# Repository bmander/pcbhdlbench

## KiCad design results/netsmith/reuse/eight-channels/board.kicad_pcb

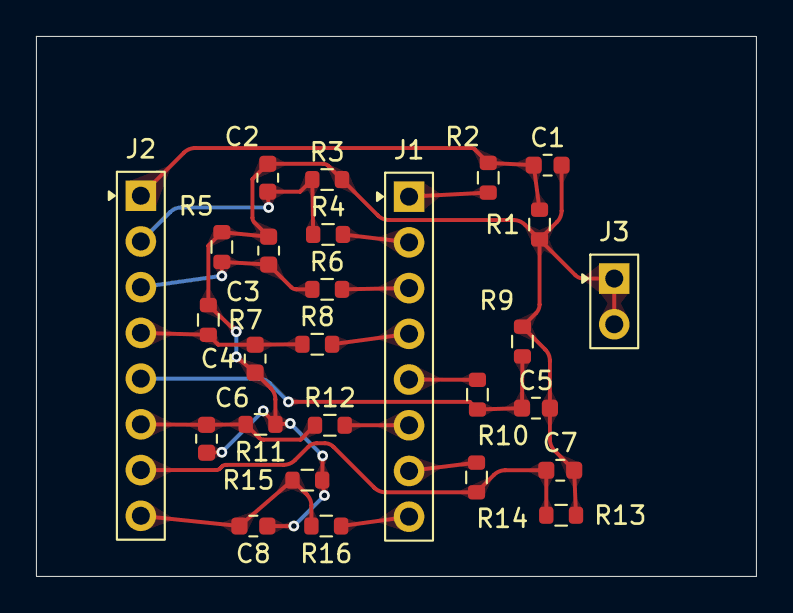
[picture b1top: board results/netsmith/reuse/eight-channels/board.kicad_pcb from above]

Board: 2 copper layers, 40.0 x 30.0 mm, 27 parts (0 on the bottom side), 17 nets.

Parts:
C1, C2, C3, C4, C5, C6, C7, C8: 100n; C_0603_1608Metric
J1, J2: Conn_01x08; PinHeader_1x08_P2.54mm_Vertical
J3: Conn_01x02; PinHeader_1x02_P2.54mm_Vertical
R1, R3, R5, R7, R9, R11, R13, R15: 100k; R_0603_1608Metric
R2, R4, R6, R8, R10, R12, R14, R16: 1k; R_0603_1608Metric

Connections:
net-ch1.c.a: C1.1, J2.1, R1.1, R2.2
net-ch1.c.b: C1.2, C2.2, C3.2, C4.2, C5.2, C6.2, C7.2, C8.2, J3.1, J3.2, R1.2, R3.2, R5.2, R7.2, R9.2, R11.2, R13.2, R15.2
net-ch1.rs.a: J1.1, R2.1
net-ch2.c.a: C2.1, J2.2, R3.1, R4.2
net-ch2.rs.a: J1.2, R4.1
net-ch3.c.a: C3.1, J2.3, R5.1, R6.2
net-ch3.rs.a: J1.3, R6.1
net-ch4.c.a: C4.1, J2.4, R7.1, R8.2
net-ch4.rs.a: J1.4, R8.1
net-ch5.c.a: C5.1, J2.5, R9.1, R10.2
net-ch5.rs.a: J1.5, R10.1
net-ch6.c.a: C6.1, J2.6, R11.1, R12.2
net-ch6.rs.a: J1.6, R12.1
net-ch7.c.a: C7.1, J2.7, R13.1, R14.2
net-ch7.rs.a: J1.7, R14.1
net-ch8.c.a: C8.1, J2.8, R15.1, R16.2
net-ch8.rs.a: J1.8, R16.1

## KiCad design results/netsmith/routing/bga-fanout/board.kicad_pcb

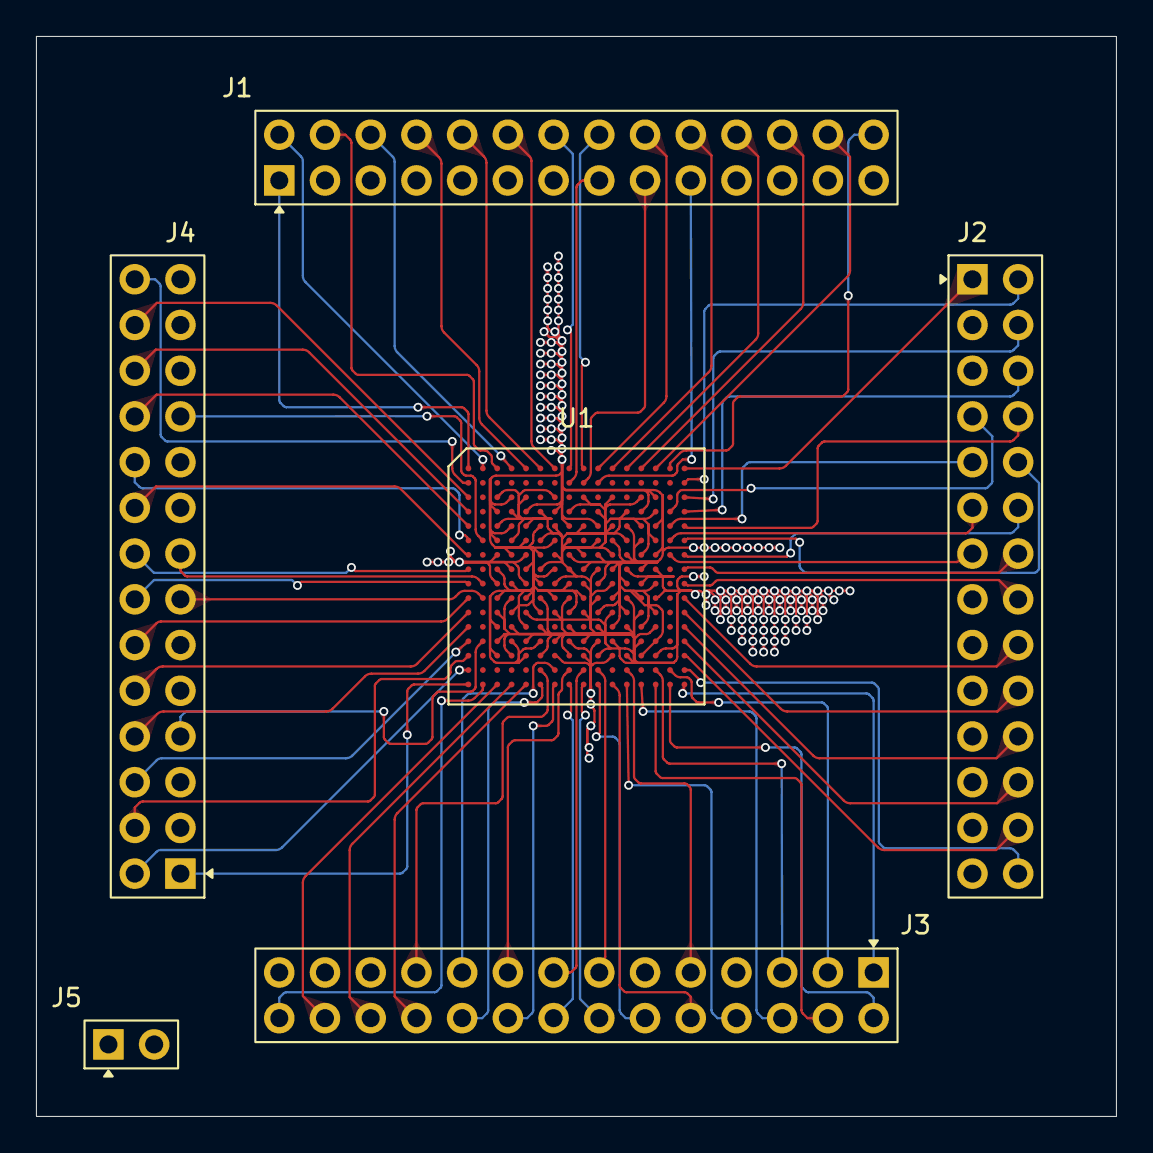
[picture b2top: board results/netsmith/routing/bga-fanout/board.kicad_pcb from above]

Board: 4 copper layers, 60.0 x 60.0 mm, 6 parts (0 on the bottom side), 114 nets.

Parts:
J1, J2, J3, J4: Header2x14; PinHeader_pins14_pitch2.54mm_rows2
J5: Conn_01x02; PinHeader_1x02_P2.54mm_Vertical
U1: Bga256; BGA-256_14.0x14.0mm_Layout16x16_P0.8mm_Ball0.45mm_Pad0.32mm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

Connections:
GND: J5.2, U1.C3, U1.C5, U1.C7, U1.C9, U1.C11, U1.C13, U1.D4, U1.D6, U1.D8, U1.D10, U1.D12, U1.D14, U1.E3, U1.E5, U1.E7, U1.E9, U1.E11, U1.E13, U1.F4, U1.F6, U1.F8, U1.F10, U1.F12, U1.F14, U1.G3, U1.G5, U1.G7, U1.G9, U1.G11, U1.G13, U1.H4, U1.H6, U1.H8, U1.H10, U1.H12, U1.H14, U1.J3, U1.J5, U1.J7, U1.J9, U1.J11, U1.J13, U1.K4, U1.K6, U1.K8, U1.K10, U1.K12, U1.K14, U1.L3, U1.L5, U1.L7, U1.L9, U1.L11, U1.L13, U1.M4, U1.M6, U1.M8, U1.M10, U1.M12, U1.M14, U1.N3, U1.N5, U1.N7, U1.N9, U1.N11, U1.N13, U1.P4, U1.P6, U1.P8, U1.P10, U1.P12, U1.P14
VCC: J5.1, U1.C4, U1.C6, U1.C8, U1.C10, U1.C12, U1.C14, U1.D3, U1.D5, U1.D7, U1.D9, U1.D11, U1.D13, U1.E4, U1.E6, U1.E8, U1.E10, U1.E12, U1.E14, U1.F3, U1.F5, U1.F7, U1.F9, U1.F11, U1.F13, U1.G4, U1.G6, U1.G8, U1.G10, U1.G12, U1.G14, U1.H3, U1.H5, U1.H7, U1.H9, U1.H11, U1.H13, U1.J4, U1.J6, U1.J8, U1.J10, U1.J12, U1.J14, U1.K3, U1.K5, U1.K7, U1.K9, U1.K11, U1.K13, U1.L4, U1.L6, U1.L8, U1.L10, U1.L12, U1.L14, U1.M3, U1.M5, U1.M7, U1.M9, U1.M11, U1.M13, U1.N4, U1.N6, U1.N8, U1.N10, U1.N12, U1.N14, U1.P3, U1.P5, U1.P7, U1.P9, U1.P11, U1.P13
net-j1.p1: J1.1, U1.A1
net-j1.p2: J1.2, U1.A2
net-j1.p3: J1.3, U1.B2
net-j1.p4: J1.4, U1.A3
net-j1.p5: J1.5, U1.B3
net-j1.p6: J1.6, U1.A4
net-j1.p7: J1.7, U1.B4
net-j1.p8: J1.8, U1.A5
net-j1.p9: J1.9, U1.B5
net-j1.p10: J1.10, U1.A6
net-j1.p11: J1.11, U1.B6
net-j1.p12: J1.12, U1.A7
net-j1.p13: J1.13, U1.B7
net-j1.p14: J1.14, U1.A8
net-j1.p15: J1.15, U1.B8
net-j1.p16: J1.16, U1.A9
net-j1.p17: J1.17, U1.B9
net-j1.p18: J1.18, U1.A10
net-j1.p19: J1.19, U1.B10
net-j1.p20: J1.20, U1.A11
net-j1.p21: J1.21, U1.B11
net-j1.p22: J1.22, U1.A12
net-j1.p23: J1.23, U1.B12
net-j1.p24: J1.24, U1.A13
net-j1.p25: J1.25, U1.B13
net-j1.p26: J1.26, U1.A14
net-j1.p27: J1.27, U1.B14
net-j1.p28: J1.28, U1.A15
net-j2.p1: J2.1, U1.A16
net-j2.p2: J2.2, U1.B16
net-j2.p3: J2.3, U1.B15
net-j2.p4: J2.4, U1.C16
net-j2.p5: J2.5, U1.C15
net-j2.p6: J2.6, U1.D16
net-j2.p7: J2.7, U1.D15
net-j2.p8: J2.8, U1.E16
net-j2.p9: J2.9, U1.E15
net-j2.p10: J2.10, U1.F16
net-j2.p11: J2.11, U1.F15
net-j2.p12: J2.12, U1.G16
net-j2.p13: J2.13, U1.G15
net-j2.p14: J2.14, U1.H16
net-j2.p15: J2.15, U1.H15
net-j2.p16: J2.16, U1.J16
net-j2.p17: J2.17, U1.J15
net-j2.p18: J2.18, U1.K16
net-j2.p19: J2.19, U1.K15
net-j2.p20: J2.20, U1.L16
net-j2.p21: J2.21, U1.L15
net-j2.p22: J2.22, U1.M16
net-j2.p23: J2.23, U1.M15
net-j2.p24: J2.24, U1.N16
net-j2.p25: J2.25, U1.N15
net-j2.p26: J2.26, U1.P16
net-j2.p27: J2.27, U1.P15
net-j2.p28: J2.28, U1.R16
net-j3.p1: J3.1, U1.T16
net-j3.p2: J3.2, U1.T15
net-j3.p3: J3.3, U1.R15
net-j3.p4: J3.4, U1.T14
net-j3.p5: J3.5, U1.R14
net-j3.p6: J3.6, U1.T13
net-j3.p7: J3.7, U1.R13
net-j3.p8: J3.8, U1.T12
net-j3.p9: J3.9, U1.R12
net-j3.p10: J3.10, U1.T11
net-j3.p11: J3.11, U1.R11
net-j3.p12: J3.12, U1.T10
net-j3.p13: J3.13, U1.R10
net-j3.p14: J3.14, U1.T9
net-j3.p15: J3.15, U1.R9
net-j3.p16: J3.16, U1.T8
net-j3.p17: J3.17, U1.R8
net-j3.p18: J3.18, U1.T7
net-j3.p19: J3.19, U1.R7
net-j3.p20: J3.20, U1.T6
net-j3.p21: J3.21, U1.R6
net-j3.p22: J3.22, U1.T5
net-j3.p23: J3.23, U1.R5
net-j3.p24: J3.24, U1.T4
net-j3.p25: J3.25, U1.R4
net-j3.p26: J3.26, U1.T3
net-j3.p27: J3.27, U1.R3
net-j3.p28: J3.28, U1.T2
net-j4.p1: J4.1, U1.T1
net-j4.p2: J4.2, U1.R1
net-j4.p3: J4.3, U1.R2
net-j4.p4: J4.4, U1.P1
net-j4.p5: J4.5, U1.P2
net-j4.p6: J4.6, U1.N1
net-j4.p7: J4.7, U1.N2
net-j4.p8: J4.8, U1.M1
net-j4.p9: J4.9, U1.M2
net-j4.p10: J4.10, U1.L1
net-j4.p11: J4.11, U1.L2
net-j4.p12: J4.12, U1.K1
net-j4.p13: J4.13, U1.K2
net-j4.p14: J4.14, U1.J1
net-j4.p15: J4.15, U1.J2
net-j4.p16: J4.16, U1.H1
net-j4.p17: J4.17, U1.H2
net-j4.p18: J4.18, U1.G1
net-j4.p19: J4.19, U1.G2
net-j4.p20: J4.20, U1.F1
net-j4.p21: J4.21, U1.F2
net-j4.p22: J4.22, U1.E1
net-j4.p23: J4.23, U1.E2
net-j4.p24: J4.24, U1.D1
net-j4.p25: J4.25, U1.D2
net-j4.p26: J4.26, U1.C1
net-j4.p27: J4.27, U1.C2
net-j4.p28: J4.28, U1.B1

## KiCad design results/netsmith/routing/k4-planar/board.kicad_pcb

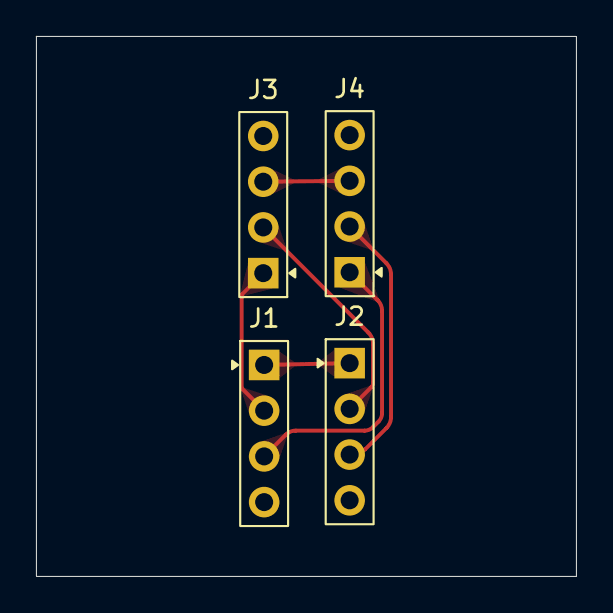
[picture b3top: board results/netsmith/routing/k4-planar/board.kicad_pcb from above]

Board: 2 copper layers, 30.0 x 30.0 mm, 4 parts (0 on the bottom side), 6 nets.

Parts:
J1, J2, J3, J4: Conn_01x04; PinHeader_1x04_P2.54mm_Vertical

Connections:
net-j1.p1: J1.1, J2.1
net-j1.p2: J1.2, J3.1
net-j1.p3: J1.3, J4.1
net-j2.p2: J2.2, J3.2
net-j2.p3: J2.3, J4.2
net-j3.p3: J3.3, J4.3

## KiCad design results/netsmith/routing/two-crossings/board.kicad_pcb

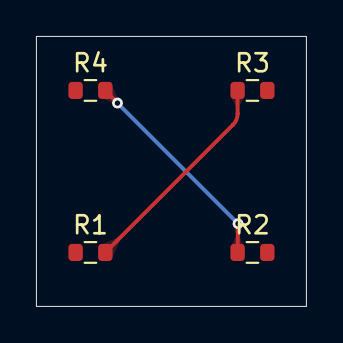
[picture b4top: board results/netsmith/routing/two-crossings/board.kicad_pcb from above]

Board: 2 copper layers, 15.0 x 15.0 mm, 4 parts (0 on the bottom side), 2 nets.

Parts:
R1, R2, R3, R4: 1k; R_0603_1608Metric

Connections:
net-r1.b: R1.2, R3.1
net-r2.a: R2.1, R4.2
